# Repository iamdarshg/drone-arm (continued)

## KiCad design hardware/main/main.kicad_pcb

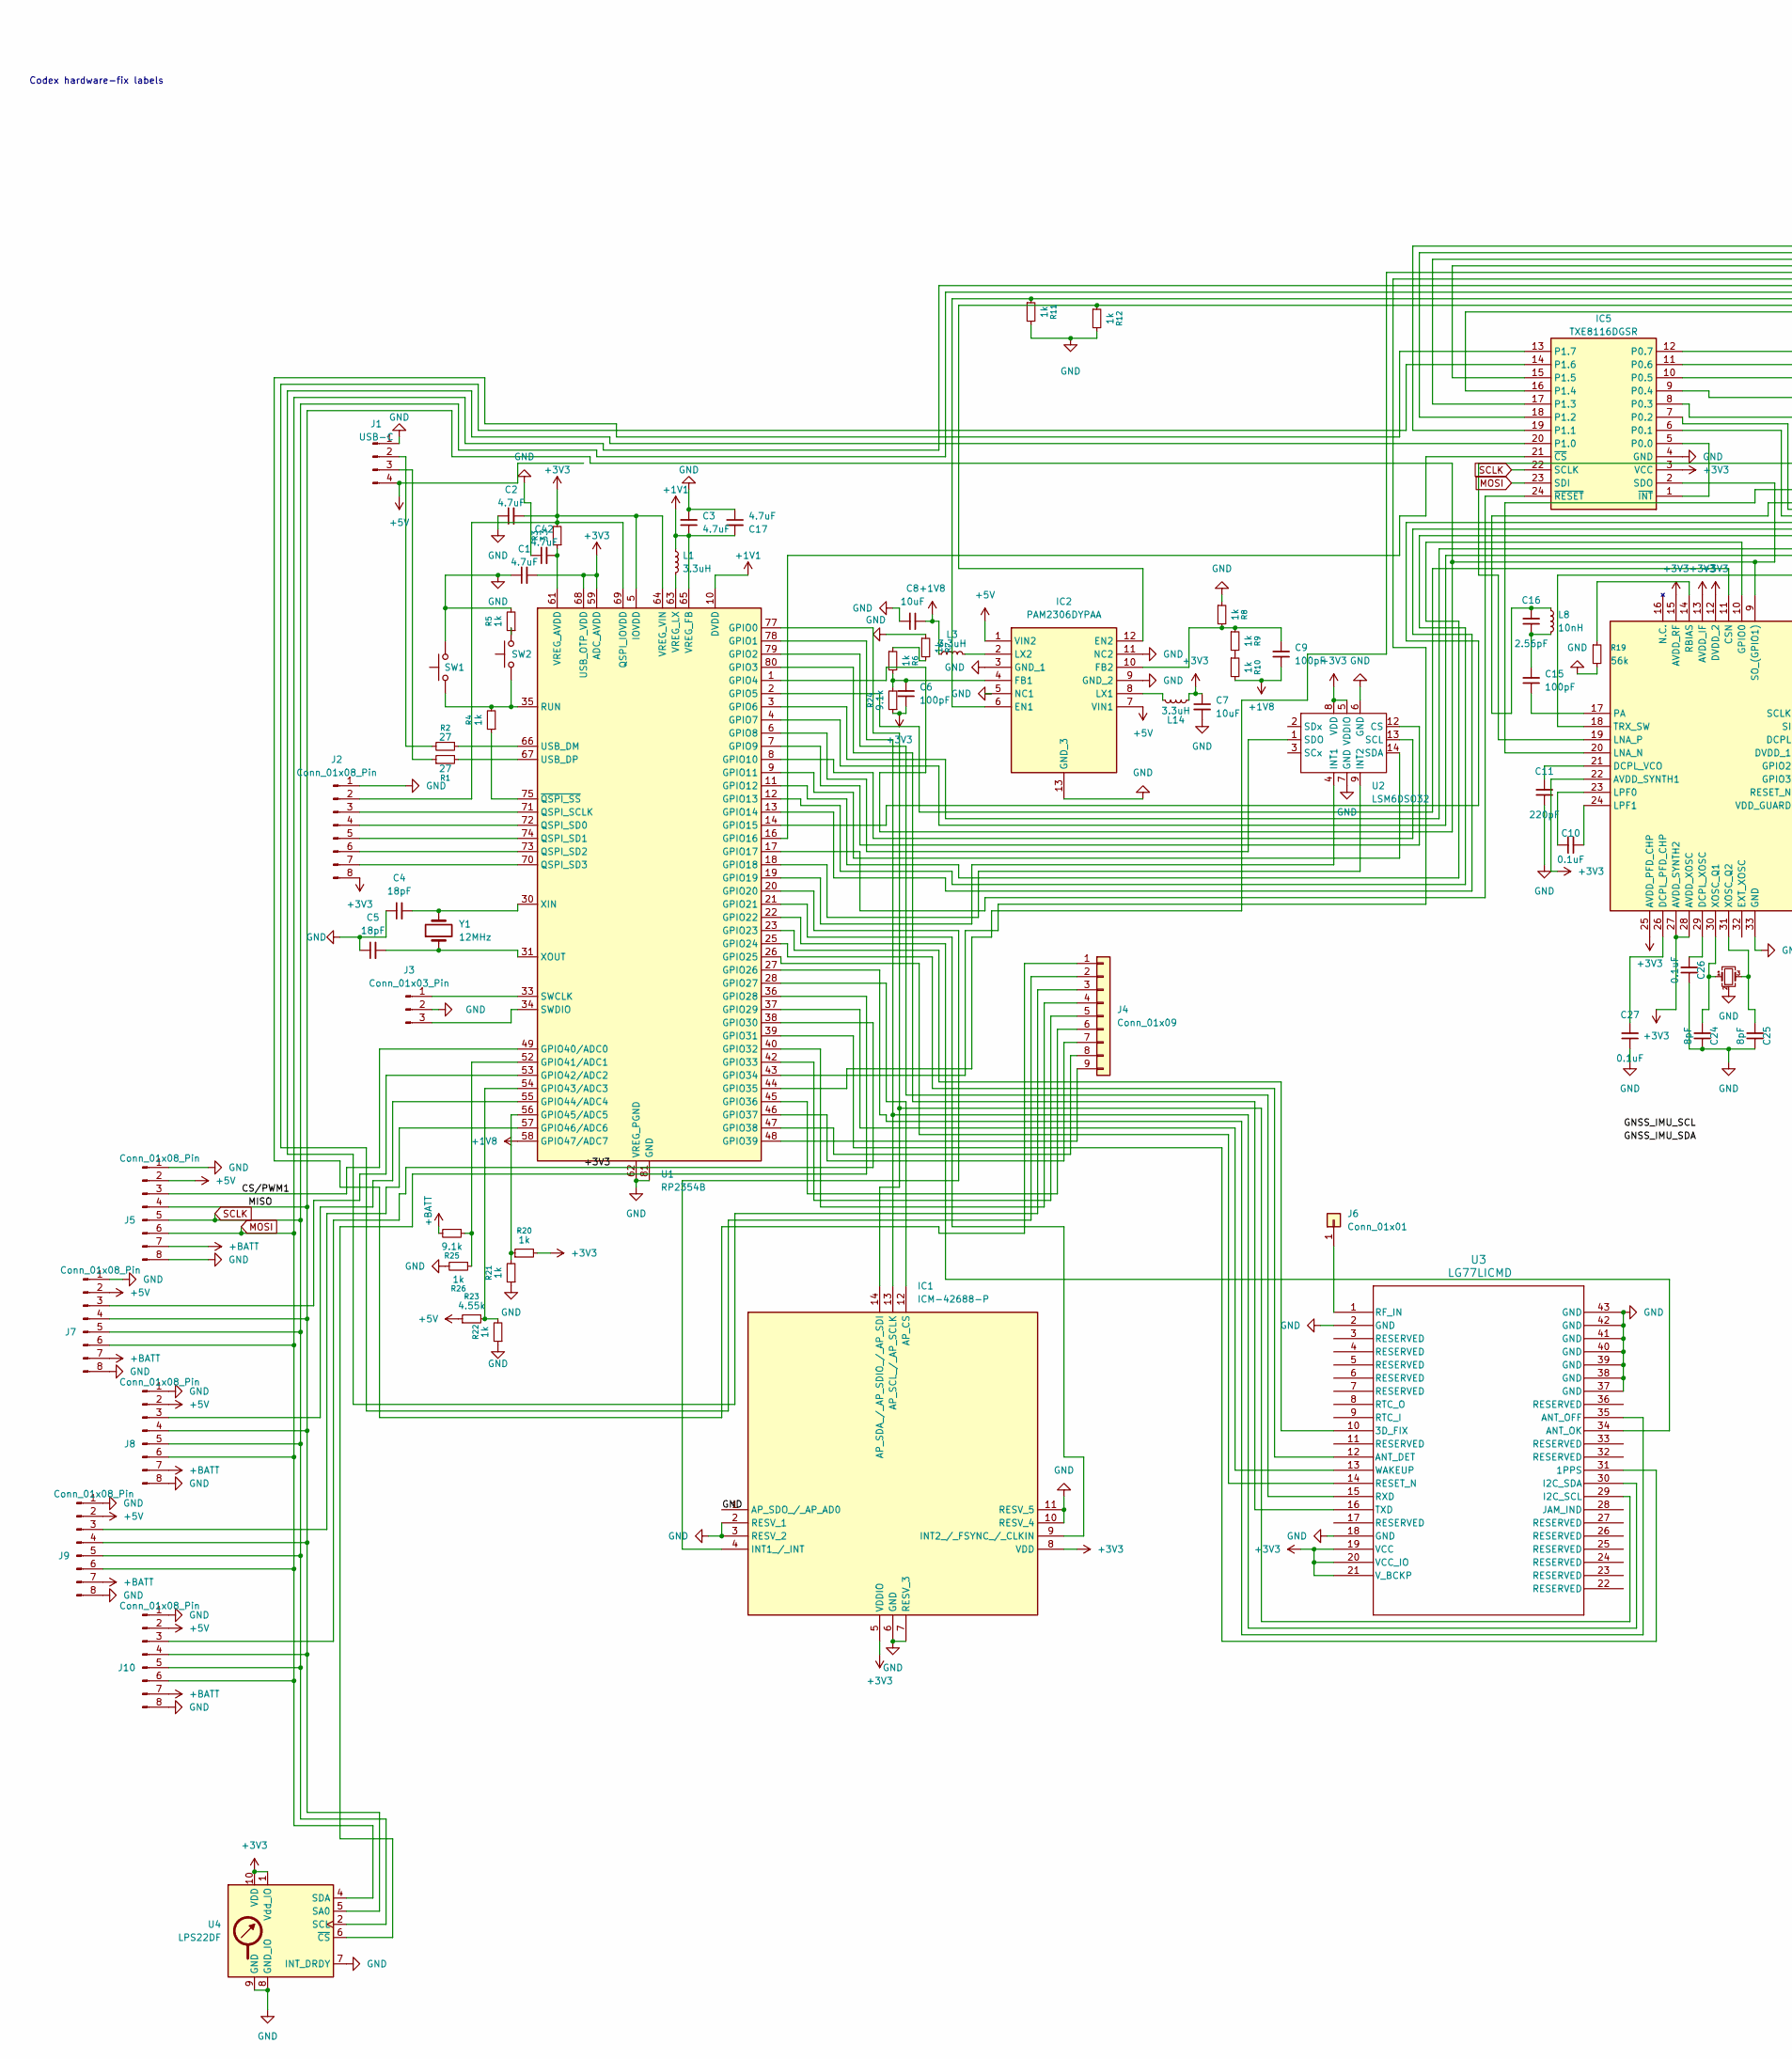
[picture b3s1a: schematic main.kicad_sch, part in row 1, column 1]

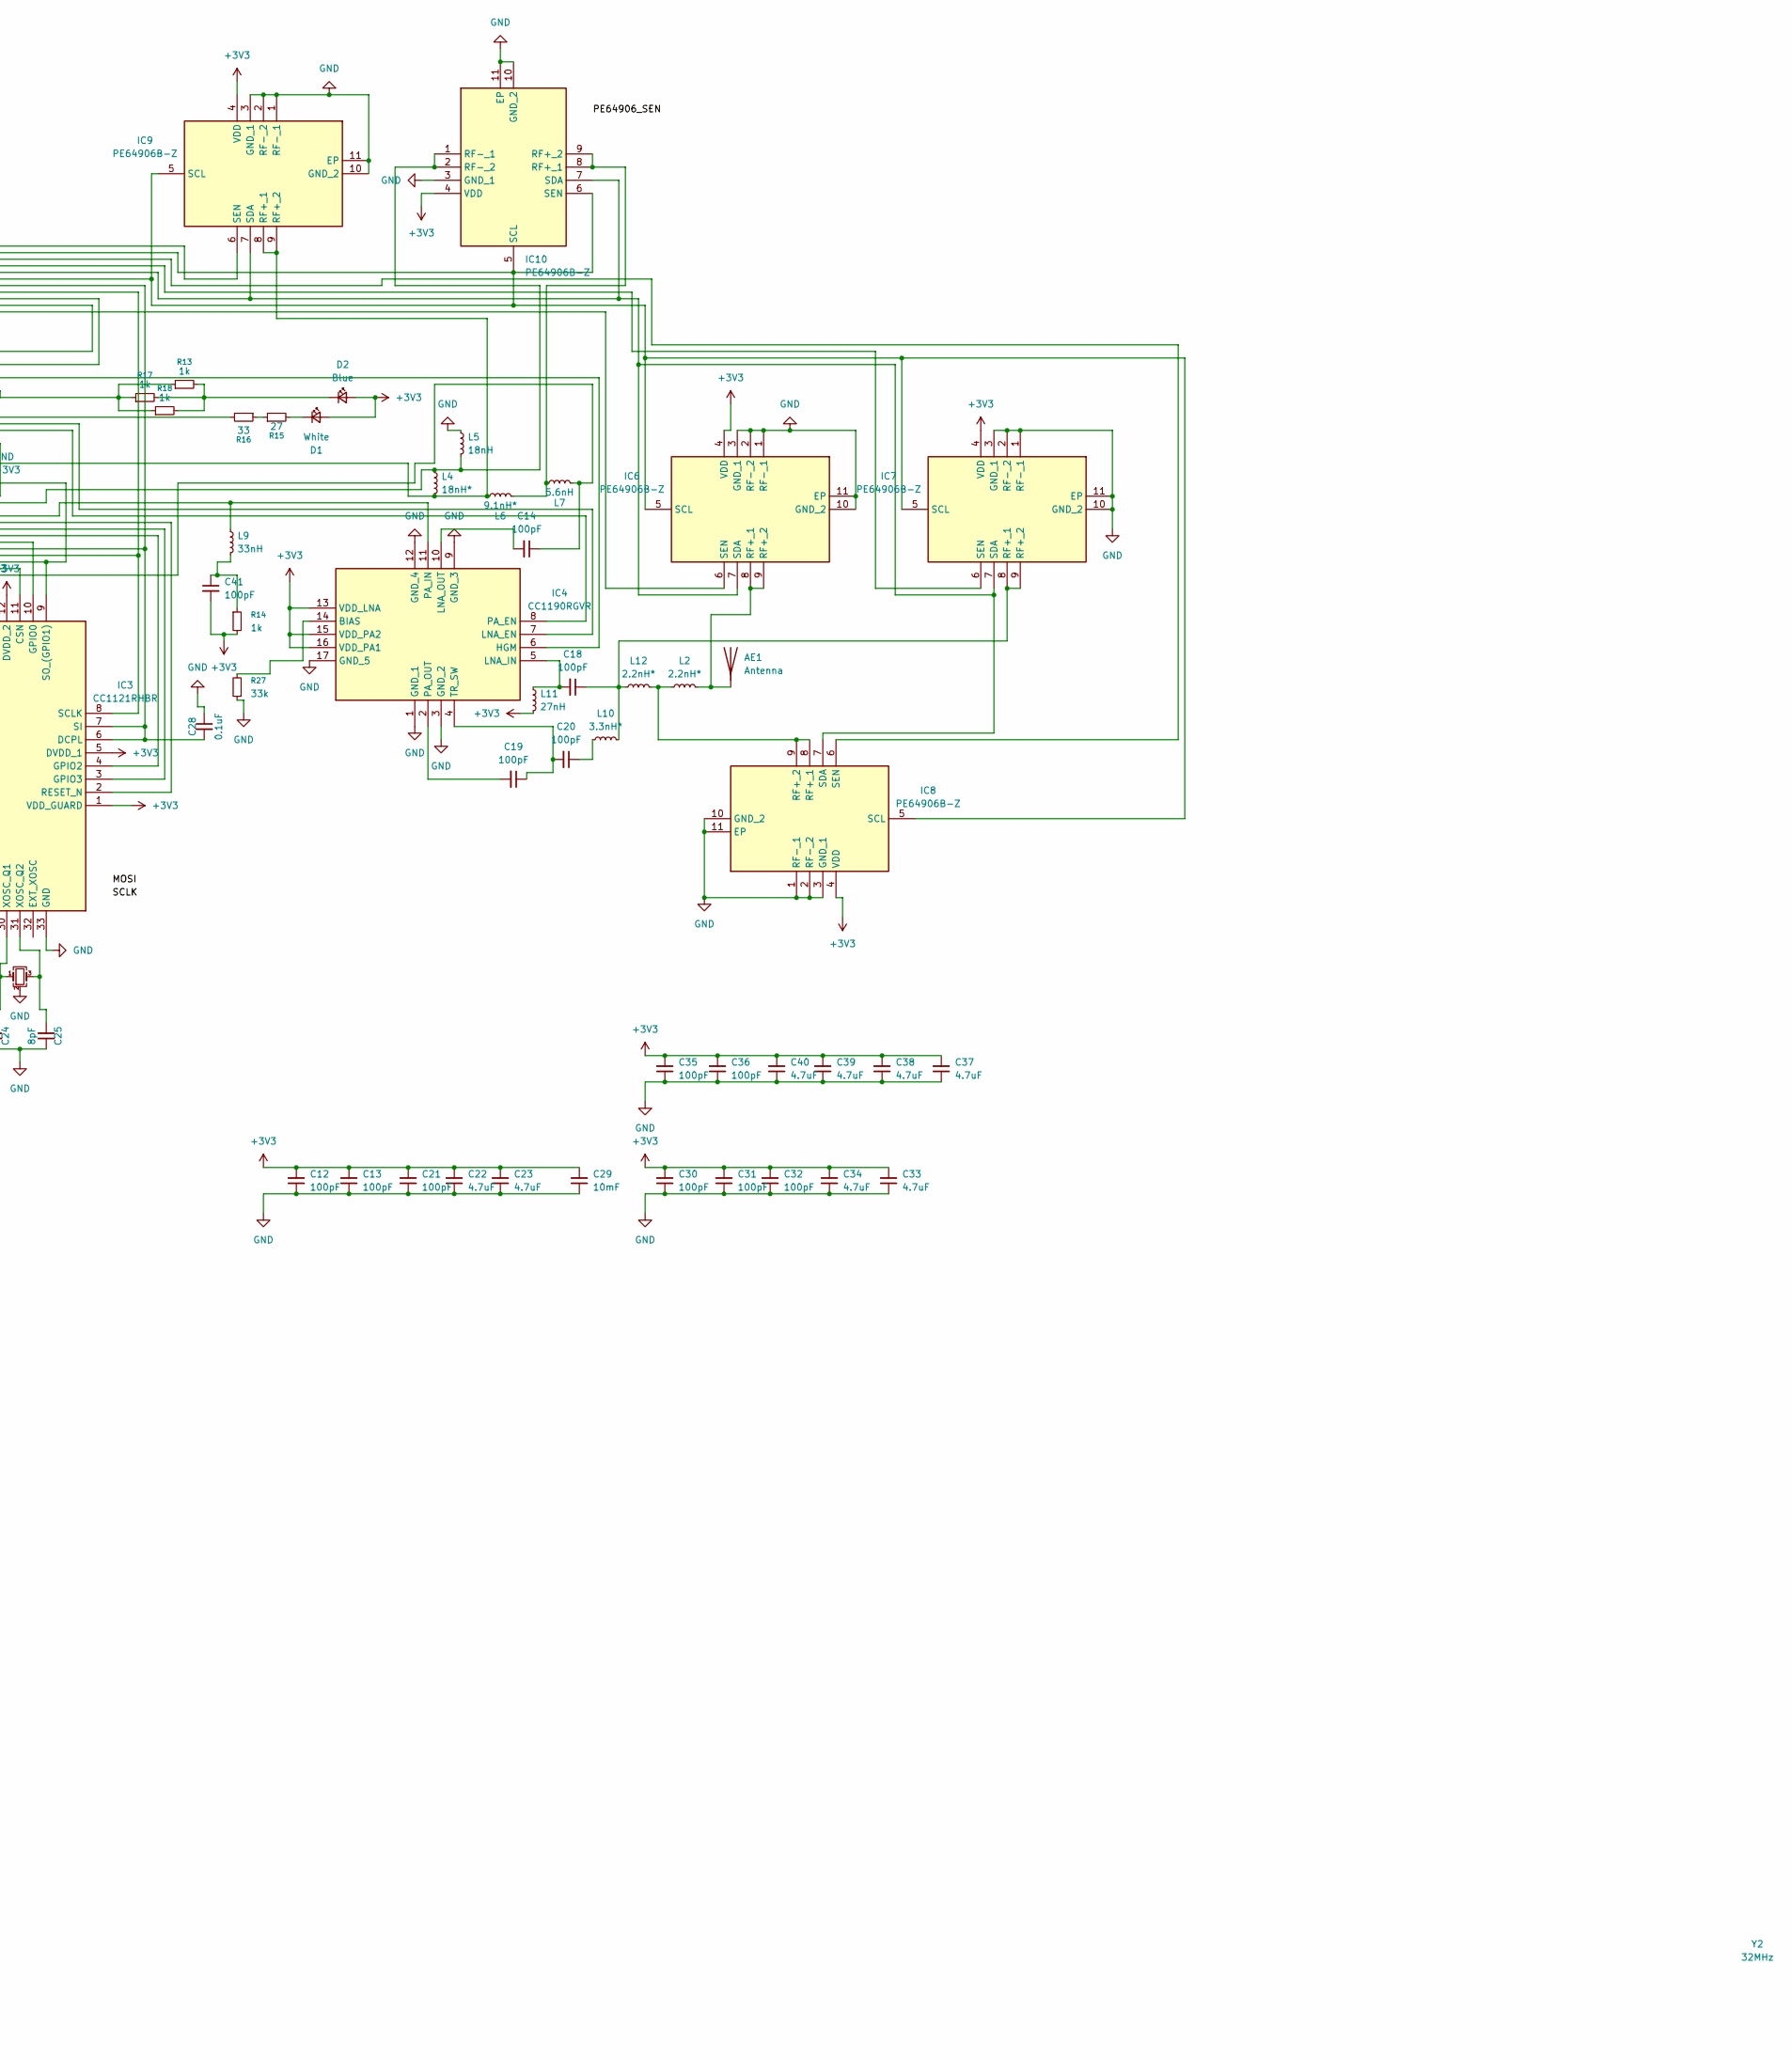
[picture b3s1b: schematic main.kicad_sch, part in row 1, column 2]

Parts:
AE1: Antenna; Texas_SWRA416_868MHz_915MHz
C1, C2, C3, C17, C22, C23, C33, C34, C37, C38, C39, C40, C42: 4.7uF; C_0805_2012Metric
C4, C5: 18pF; C_0402_1005Metric
C6, C9, C12, C13, C14, C15, C18, C19, C20, C21, C30, C31, C32, C35, C36, C41: 100pF; C_0201_0603Metric
C7, C8: 10uF; C_0805_2012Metric
C10, C26, C27, C28: 0.1uF; C_0201_0603Metric
C11: 220pF; C_0402_1005Metric
C16: 2.56pF; C_0201_0603Metric
C24, C25: 8pF; C_0402_1005Metric
C29: 10mF; CP_Radial_D5.0mm_P2.50mm
D1: White; LED_0201_0603Metric
D2: Blue; LED_0201_0603Metric
IC1: ICM-42688-P; IIM42352; Manufacturer_Part_Number ICM-42688-P; Mouser Part Number 410-ICM-42688-P
IC2: PAM2306DYPAA; SON45P300X300X80-13N; Manufacturer_Part_Number PAM2306DYPAA; Mouser Part Number 621-PAM2306DYPAA
IC3: CC1121RHBR; QFN50P500X500X100-33N-D; Manufacturer_Part_Number CC1121RHBR; Mouser Part Number 595-CC1121RHBR
IC4: CC1190RGVR; QFN65P400X400X100-17N-D; Manufacturer_Part_Number CC1190RGVR; Mouser Part Number 595-CC1190RGVR
IC5: TXE8116DGSR; SOP50P490X110-24N; Manufacturer_Part_Number TXE8116DGSR
IC6, IC7, IC8, IC9, IC10: PE64906B-Z; QFN50P200X200X60-11N-D; Manufacturer_Part_Number PE64906B-Z; Mouser Part Number 81-PE64906B-Z
J1: USB-C; PinHeader_1x04_P2.54mm_Vertical
J2: Conn_01x08_Pin; PinHeader_2x04_P1.27mm_Vertical
J3: Conn_01x03_Pin; PinHeader_1x03_P2.54mm_Vertical
J4: Conn_01x09; PinHeader_1x09_P2.54mm_Vertical
J5, J7, J8, J9, J10: Conn_01x08_Pin; PinHeader_1x08_P1.27mm_Vertical
J6: Conn_01x01; SolderWire-0.5sqmm_1x01_D0.9mm_OD2.3mm
L1: 3.3uH; L_0806_2016Metric
L2, L12: 2.2nH*; L_0402_1005Metric
L3, L14: 3.3uH; L_1210_3225Metric_Pad1.42x2.65mm_HandSolder
L4: 18nH*; L_01005_0402Metric
L5: 18nH; L_01005_0402Metric
L6: 9.1nH*; L_0402_1005Metric
L7: 5.6nH; L_0402_1005Metric
L8: 10nH; L_0805_2012Metric
L9: 33nH; L_0402_1005Metric
L10: 3.3nH*; L_0201_0603Metric
L11: 27nH; L_0201_0603Metric
R1, R2, R15: 27; R_0402_1005Metric
R3, R16: 33; R_1206_3216Metric
R4, R5, R6, R7, R8, R9, R10, R11, R12, R13, R14, R17, R18, R20, R21, R22, R26: 1k; R_0201_0603Metric
R19: 56k; R_0402_1005Metric
R23: 4.55k
R24, R25: 9.1k; R_0201_0603Metric
R27: 33k; R_0201_0603Metric
SW1, SW2: SW_Push; PinHeader_1x02_P2.54mm_Vertical
U1: RP2354B; QFN-80-1EP_10x10mm_P0.4mm_EP3.4x3.4mm
U2: LSM6DSO32; LGA-14_3x2.5mm_P0.5mm_LayoutBorder3x4y
U3: LG77LICMD; LG77L_QWS
U4: LPS22DF; ST_HLGA-10_2x2mm_P0.5mm_LayoutBorder3x2y
Y1: 12MHz; Crystal_SMD_ECS_CSM3X-2Pin_7.6x4.1mm
Y2: 32MHz; Crystal_SMD_3225-4Pin_3.2x2.5mm

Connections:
+1V1: C3.1, C17.2, L1.1, U1.10 (DVDD), U1.32 (DVDD), U1.51 (DVDD), U1.65 (VREG_FB)
+1V8: C8.1, C9.1, L3.1, R10.2, U1.58 (GPIO47/ADC7)
+3V3: C1.2, C2.2, C6.1, C7.1, C12.2, C13.2, C21.2, C22.2, C23.2, C29.2, C30.2, C31.2, C32.2, C33.2, C34.2, C35.2, C36.2, C37.2, C38.2, C39.2, C40.2, C41.2, D1.2 (A), D2.2 (A), IC1.5 (VDDIO), IC1.8 (VDD), IC3.1 (VDD_GUARD), IC3.5 (DVDD_1), IC3.12 (DVDD_2), IC3.13 (AVDD_IF), IC3.15 (AVDD_RF), IC3.22 (AVDD_SYNTH1), IC3.25 (AVDD_PFD_CHP), IC3.27 (AVDD_SYNTH2), IC3.28 (AVDD_XOSC), IC4.13 (VDD_LNA), IC4.15 (VDD_PA2), IC4.16 (VDD_PA1), IC5.3 (VCC), IC6.4 (VDD), IC7.4 (VDD), IC8.4 (VDD), IC9.4 (VDD), IC10.4 (VDD), J2.2, J2.8, L11.2, L14.1, R3.2, R14.2, R20.2, R24.1, U1.5 (IOVDD), U1.15 (IOVDD), U1.24 (IOVDD), U1.29 (IOVDD), U1.41 (IOVDD), U1.50 (IOVDD), U1.59 (ADC_AVDD), U1.60 (IOVDD), U1.64 (VREG_VIN), U1.68 (USB_OTP_VDD), U1.69 (QSPI_IOVDD), U1.76 (IOVDD), U2.5 (VDDIO), U2.8 (VDD), U3.19 (VCC), U3.20 (VCC_IO), U3.21 (V_BCKP), U4.1 (Vdd_IO), U4.10 (VDD)
+5V: IC2.1 (VIN2), IC2.7 (VIN1), J1.4, J5.2, J7.2, J8.2, J9.2, J10.2, R23.1
+BATT: J5.7, J7.7, J8.7, J9.7, J10.7, R25.2
/CS/PWM1: J5.3, U1.49 (GPIO40/ADC0)
/MISO: IC3.9 (SO_(GPIO1)), IC5.2 (SDO), J5.4, J7.4, J8.4, J9.4, J10.4, U1.1 (GPIO4), U4.5 (SA0)
/SCLK: IC3.8 (SCLK), IC5.22 (SCLK), J5.5, J7.5, J8.5, J9.5, J10.5, U1.4 (GPIO7), U4.2 (SCL)
GND: C1.1, C2.1, C3.2, C4.1, C5.1, C7.2, C8.2, C11.1, C12.1, C13.1, C17.1, C21.1, C22.1, C23.1, C24.1, C25.1, C26.1, C27.1, C28.1, C29.1, C30.1, C31.1, C32.1, C33.1, C34.1, C35.1, C36.1, C37.1, C38.1, C39.1, C40.1, C42.1, IC1.1 (AP_SDO_/_AP_AD0), IC1.2 (RESV_1), IC1.3 (RESV_2), IC1.6 (GND), IC1.7 (RESV_3), IC1.10 (RESV_4), IC1.11 (RESV_5), IC2.3 (GND_1), IC2.5 (NC1), IC2.9 (GND_2), IC2.11 (NC2), IC2.13 (GND_3), IC3.33 (GND), IC4.1 (GND_1), IC4.3 (GND_2), IC4.9 (GND_3), IC4.12 (GND_4), IC4.17 (GND_5), IC5.4 (GND), IC6.1 (RF-_1), IC6.2 (RF-_2), IC6.3 (GND_1), IC6.10 (GND_2), IC6.11 (EP), IC7.1 (RF-_1), IC7.2 (RF-_2), IC7.3 (GND_1), IC7.10 (GND_2), IC7.11 (EP), IC8.1 (RF-_1), IC8.2 (RF-_2), IC8.3 (GND_1), IC8.10 (GND_2), IC8.11 (EP), IC9.1 (RF-_1), IC9.2 (RF-_2), IC9.3 (GND_1), IC9.10 (GND_2), IC9.11 (EP), IC10.3 (GND_1), IC10.10 (GND_2), IC10.11 (EP), J1.1, J2.1, J3.2, J5.1, J5.8, J7.1, J7.8, J8.1, J8.8, J9.1, J9.8, J10.1, J10.8, L5.1, R5.2, R7.1, R8.1, R11.2, R12.2, R19.2, R21.1, R22.1, R26.2, R27.1, SW1.2, U1.62 (VREG_PGND), U1.81 (GND), U2.6 (GND), U2.7 (GND), U3.2 (GND), U3.18 (GND), U3.37 (GND), U3.38 (GND), U3.39 (GND), U3.40 (GND), U3.41 (GND), U3.42 (GND), U3.43 (GND), U4.3 (GND), U4.7 (INT_DRDY), U4.8 (GND_IO), U4.9 (GND), Y2.2 (G), Y2.4 (G)
unnamed: AE1.1 (A), IC6.8 (RF+_1), IC6.9 (RF+_2), L2.2
unnamed: C15.2, C16.1, L8.2
unnamed: C20.1, L10.1
unnamed: C41.1, L9.2, R14.1
unnamed: D1.1 (K), R15.2
unnamed: D2.1 (K), R13.2, R17.2, R18.2
unnamed: IC1.12 (AP_CS), U1.28 (GPIO27)
unnamed: IC1.4 (INT1_/_INT), U1.20 (GPIO20)
unnamed: IC1.9 (INT2_/_FSYNC_/_CLKIN), U1.21 (GPIO21)
unnamed: IC2.6 (EN1), IC5.11 (P0.6), R11.1
unnamed: IC2.12 (EN2), IC5.12 (P0.7), R12.1
unnamed: C6.2, IC2.4 (FB1), R6.2, R24.2
unnamed: C9.2, IC2.10 (FB2), R8.2, R9.1
unnamed: IC2.8 (LX1), L14.2
unnamed: IC2.2 (LX2), L3.2
unnamed: IC3.11 (CSN), U1.2 (GPIO5)
unnamed: C27.2, IC3.26 (DCPL_PFD_CHP)
unnamed: C11.2, IC3.21 (DCPL_VCO)
unnamed: C26.2, IC3.29 (DCPL_XOSC)
unnamed: IC3.10 (GPIO0), U1.11 (GPIO12)
unnamed: IC3.4 (GPIO2), U1.12 (GPIO13)
unnamed: IC3.3 (GPIO3), U1.13 (GPIO14)
unnamed: IC3.19 (LNA_P), IC9.8 (RF+_1), IC9.9 (RF+_2), L4.2, L6.1
unnamed: C10.2, IC3.23 (LPF0)
unnamed: C10.1, IC3.24 (LPF1)
unnamed: C15.1, IC3.17 (PA)
unnamed: IC3.14 (RBIAS), R19.1
unnamed: IC3.2 (RESET_N), U1.14 (GPIO15)
unnamed: C14.1, IC3.18 (TRX_SW), L7.2
unnamed: C24.2, IC3.30 (XOSC_Q1), Y2.1
unnamed: C25.2, IC3.31 (XOSC_Q2), Y2.3
unnamed: IC4.14 (BIAS), R27.2
unnamed: IC4.6 (HGM), IC5.10 (P0.5)
unnamed: IC4.7 (LNA_EN), IC5.7 (P0.2)
unnamed: C18.2, IC4.5 (LNA_IN), L11.1
unnamed: C14.2, IC4.10 (LNA_OUT)
unnamed: IC4.8 (PA_EN), IC5.6 (P0.1)
unnamed: C16.2, IC4.11 (PA_IN), L8.1, L9.1
unnamed: C19.2, IC4.2 (PA_OUT)
unnamed: C19.1, C20.2, IC4.4 (TR_SW)
unnamed: IC5.1 (~INT), IC5.5 (P0.0)
unnamed: IC5.8 (P0.3), R16.2
unnamed: IC5.9 (P0.4), R13.1, R17.1, R18.1
unnamed: IC5.20 (P1.0), J4.3
unnamed: IC5.19 (P1.1), IC9.6 (SEN)
unnamed: IC5.17 (P1.3), IC8.6 (SEN)
unnamed: IC5.16 (P1.4), IC6.6 (SEN)
unnamed: IC5.15 (P1.5), IC7.6 (SEN)
unnamed: IC5.14 (P1.6), J4.2
unnamed: IC5.13 (P1.7), J4.1
unnamed: IC5.21 (~CS), U1.16 (GPIO16)
unnamed: IC5.24 (~RESET), U1.17 (GPIO17)
unnamed: C18.1, IC7.8 (RF+_1), IC7.9 (RF+_2), L10.2, L12.1
unnamed: IC8.8 (RF+_1), IC8.9 (RF+_2), L2.1, L12.2
unnamed: IC10.8 (RF+_1), IC10.9 (RF+_2), L6.2, L7.1
unnamed: IC3.20 (LNA_N), IC10.1 (RF-_1), IC10.2 (RF-_2), L4.1, L5.2
unnamed: IC6.7 (SDA), IC7.7 (SDA), IC8.7 (SDA), IC9.7 (SDA), IC10.7 (SDA), U1.44 (GPIO35)
unnamed: J1.2, R2.2
unnamed: J1.3, R1.1
unnamed: J2.3, U1.71 (QSPI_SCLK)
unnamed: J2.4, U1.72 (QSPI_SD0)
unnamed: J2.5, U1.74 (QSPI_SD1)
unnamed: J2.6, U1.73 (QSPI_SD2)
unnamed: J2.7, U1.70 (QSPI_SD3)
unnamed: J3.1, U1.33 (SWCLK)
unnamed: J3.3, U1.34 (SWDIO)
unnamed: J4.4, U1.40 (GPIO32)
unnamed: J4.5, U1.42 (GPIO33)
unnamed: J4.6, U1.45 (GPIO36)
unnamed: J4.7, U1.46 (GPIO37)
unnamed: J4.8, U1.47 (GPIO38)
unnamed: J4.9, U1.48 (GPIO39)
unnamed: J6.1, U3.1 (RF_IN)
unnamed: J7.3, U1.53 (GPIO42/ADC2)
unnamed: J8.3, U1.55 (GPIO44/ADC4)
unnamed: J9.3, U1.57 (GPIO46/ADC6)
unnamed: J10.3, U1.38 (GPIO30)
unnamed: R5.1, SW2.2
unnamed: R6.1, R7.2
unnamed: R9.2, R10.1
unnamed: R15.1, R16.1
unnamed: U1.79 (GPIO2), U3.15 (RXD)
unnamed: U1.80 (GPIO3), U3.16 (TXD)
unnamed: U1.6 (GPIO8), U2.1 (SDO)
unnamed: U1.7 (GPIO9), U2.12 (CS)
unnamed: U1.8 (GPIO10), U2.13 (SCL)
unnamed: U1.9 (GPIO11), U2.14 (SDA)
unnamed: U1.18 (GPIO18), U2.9 (INT2)
unnamed: U1.19 (GPIO19), U2.4 (INT1)
unnamed: U1.22 (GPIO22), U3.34 (ANT_OK)
unnamed: U1.23 (GPIO23), U3.10 (3D_FIX)
unnamed: U1.25 (GPIO24), U3.12 (ANT_DET)
unnamed: U1.26 (GPIO25), U3.14 (RESET_N)
unnamed: U1.27 (GPIO26), U3.35 (ANT_OFF)
unnamed: U1.36 (GPIO28), U4.6 (~CS)
unnamed: U1.37 (GPIO29), U3.13 (WAKEUP)
unnamed: U1.39 (GPIO31), U3.31 (1PPS)
unnamed: R25.1, R26.1, U1.52 (GPIO41/ADC1)
unnamed: R22.2, R23.2, U1.54 (GPIO43/ADC3)
unnamed: R20.1, R21.2, U1.56 (GPIO45/ADC5)
unnamed: R4.2, SW1.1, SW2.1, U1.35 (RUN)
unnamed: R2.1, U1.66 (USB_DM)
unnamed: R1.2, U1.67 (USB_DP)
unnamed: C42.2, R3.1, U1.61 (VREG_AVDD)
unnamed: L1.2, U1.63 (VREG_LX)
unnamed: C4.2, U1.30 (XIN), Y1.2
unnamed: C5.2, U1.31 (XOUT), Y1.1
unnamed: R4.1, U1.75 (~QSPI_SS)

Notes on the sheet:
Codex hardware-fix labels

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
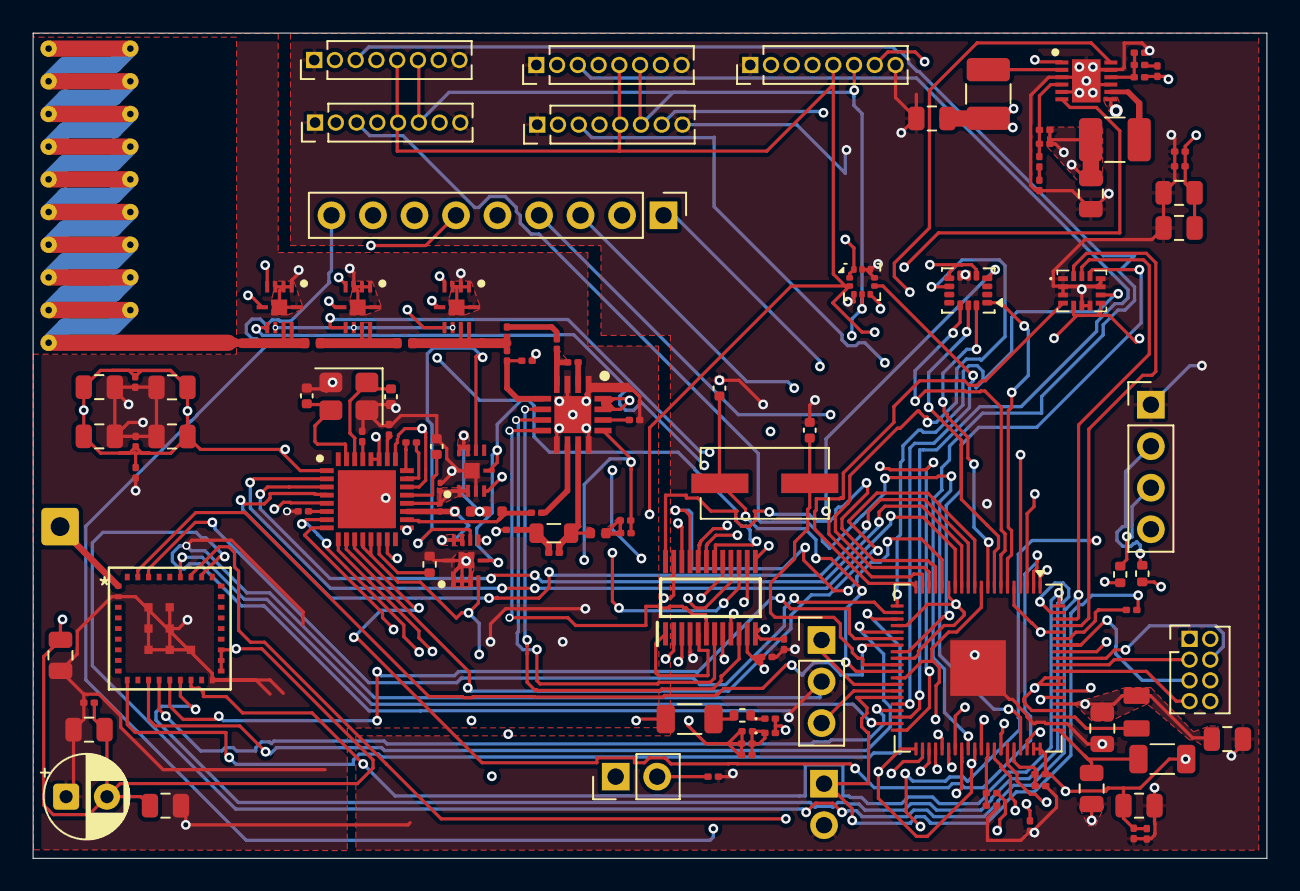
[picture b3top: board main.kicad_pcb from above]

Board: 4 copper layers, 75.5 x 50.5 mm, 112 parts (1 on the bottom side), 122 nets.

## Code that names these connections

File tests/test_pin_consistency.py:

#!/usr/bin/env python3
"""Pin-consistency test: firmware pin map vs PCB netlist pin map.

Firmware source of truth: src/board_config.h on the sdk-recreation branch.
This test reads hardware/main/rev_b/mcu_pinmap.json (generated from the
schematic netlist) and asserts that every firmware pin assignment matches
the PCB.  Run with: pytest tests/test_pin_consistency.py
"""
import json
import subprocess
import sys
from pathlib import Path

REPO = Path(__file__).resolve().parents[1]
PINMAP = REPO / "hardware/main/rev_b/mcu_pinmap.json"

# Firmware pin assignments (RP2354B GPIO numbers).
# Source: sdk-recreation branch, src/board_config.h + main Rev-B interface spec.
# The firmware repo keeps these in board_config.h; they are mirrored here so the
# test fails loudly if either side drifts.
FIRMWARE_PINS = {
    "SENS_SCLK": 0,
    "SENS_MOSI": 1,
    "SENS_MISO": 2,
    "ICM_nCS": 3,
    "LSM_nCS": 4,
    "ICM_INT1": 5,
    "ICM_INT2": 6,
    "LSM_INT1": 7,
    "LSM_INT2": 8,
    "BARO_SCL": 9,
    "BARO_SDA": 10,
    "BARO_DRDY": 11,
    "GNSS_TX": 12,
    "GNSS_RX": 13,
    "GNSS_PPS": 14,
    "GNSS_RESET_N": 15,
    "RF_SCLK": 16,
    "RF_MOSI": 17,
    "RF_MISO": 18,
    "RF_nCS": 19,
    "RF_RESET_N": 20,
    "RF_GPIO0": 21,
    "RF_GPIO2": 22,
    "RF_GPIO3": 23,
    "PA_EN": 24,
    "LNA_EN": 25,
    "HGM": 26,
    "CAN_SCK": 27,
    "CAN_MOSI": 28,
    "CAN_MISO": 29,
    "CAN_nCS": 30,
    "CAN_INT": 31,
    "STATUS_LED": 32,
    "GNSS_PWR_EN": 33,
    "PWM_ESC1": 34,
    "PWM_ESC2": 35,
    "PWM_ESC3": 36,
    "PWM_ESC4": 37,
    "PWM_ESC5": 38,
    "PWM_ESC6": 39,
}


def load_pcb_map():
    data = json.loads(PINMAP.read_text())
    out = {}
    for gpio, info in data["pins"].items():
        # normalise hierarchical net names to their leaf token
        leaf = info["net"].split("/")[-1]
        out.setdefault(leaf, []).append(int(gpio))
    return out


def test_pinmap_file_exists():
    assert PINMAP.exists(), "run tools/hardware/gen_main_pinmap.py first"


def test_every_firmware_pin_exists_on_pcb():
    pcb = load_pcb_map()
    missing = [n for n in FIRMWARE_PINS if n not in pcb]
    assert not missing, f"firmware pins absent from PCB: {missing}"


def test_gpio_numbers_match():
    pcb = load_pcb_map()
    wrong = {
        n: (FIRMWARE_PINS[n], pcb.get(n))
        for n in FIRMWARE_PINS
        if n in pcb and FIRMWARE_PINS[n] not in pcb[n]
    }
    assert not wrong, f"GPIO number mismatches firmware vs PCB: {wrong}"


def test_no_duplicate_gpio_assignment():
    seen = {}
    for n, g in FIRMWARE_PINS.items():
        assert g not in seen, f"GPIO{g} double-assigned: {seen[g]} and {n}"
        seen[g] = n


def test_esc_pwm_pins_are_contiguous():
    esc = [FIRMWARE_PINS[f"PWM_ESC{i}"] for i in range(1, 7)]
    assert esc == sorted(esc), "ESC PWM pins must be ascending"

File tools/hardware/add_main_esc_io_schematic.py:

#!/usr/bin/env python3
"""Surgically add six standard PWM ESC connectors to Main Rev B schematics."""

from __future__ import annotations

import re
import uuid
from pathlib import Path


ROOT = Path(__file__).resolve().parents[2]
MAIN_DIR = ROOT / "hardware" / "main" / "rev_b"
MCU_PATH = MAIN_DIR / "mcu.kicad_sch"
TOP_PATH = MAIN_DIR / "main_rev_b.kicad_sch"


def new_uuid() -> str:
    return str(uuid.uuid4())


def number(value: float) -> str:
    rounded = round(value, 4)
    if rounded == int(rounded):
        return str(int(rounded))
    return f"{rounded:.4f}".rstrip("0").rstrip(".")


def sexpr_end(text: str, start: int) -> int:
    depth = 0
    in_string = False
    escaped = False
    for index in range(start, len(text)):
        char = text[index]
        if in_string:
            if escaped:
                escaped = False
            elif char == "\\":
                escaped = True
            elif char == '"':
                in_string = False
            continue
        if char == '"':
            in_string = True
        elif char == "(":
            depth += 1
        elif char == ")":
            depth -= 1
            if depth == 0:
                return index + 1
    raise ValueError("Unbalanced KiCad S-expression")


def find_block(text: str, start_pattern: str, contains: str) -> tuple[int, int, str]:
    for match in re.finditer(start_pattern, text, flags=re.MULTILINE):
        start = match.start()
        end = sexpr_end(text, start)
        block = text[start:end]
        if contains in block:
            return start, end, block
    raise ValueError(f"Could not find block containing {contains!r}")


def wire_block(x1: float, y1: float, x2: float, y2: float) -> str:
    return (
        "\t(wire\n"
        "\t\t(pts\n"
        f"\t\t\t(xy {number(x1)} {number(y1)}) (xy {number(x2)} {number(y2)})\n"
        "\t\t)\n"
        "\t\t(stroke\n"
        "\t\t\t(width 0)\n"
        "\t\t\t(type default)\n"
        "\t\t)\n"
        f"\t\t(uuid \"{new_uuid()}\")\n"
        "\t)\n"
    )


def label_block(name: str, x: float, y: float, rotation: int = 0, size: float = 0.9) -> str:
    return (
        f"\t(label \"{name}\"\n"
        f"\t\t(at {number(x)} {number(y)} {rotation})\n"
        "\t\t(effects\n"
        "\t\t\t(font\n"
        f"\t\t\t\t(size {number(size)} {number(size)})\n"
        "\t\t\t)\n"
        "\t\t\t(justify left bottom)\n"
        "\t\t)\n"
        f"\t\t(uuid \"{new_uuid()}\")\n"
        "\t)\n"
    )


def hierarchical_label_block(name: str, y: float) -> str:
    return (
        f"\n\t(hierarchical_label \"{name}\"\n"
        "\t\t(shape input)\n"
        f"\t\t(at 20.32 {number(y)} 0.0000)\n"
        "\t\t(effects\n"
        "\t\t\t(font\n"
        "\t\t\t\t(size 0.9 0.9)\n"
        "\t\t\t)\n"
        "\t\t\t(justify left)\n"
        "\t\t)\n"
        f"\t\t(uuid \"{new_uuid()}\")\n"
        "\t)"
    )


def sheet_pin_block(name: str, x: float, y: float, rotation: int, justify: str) -> str:
    return (
        f"\t\t(pin \"{name}\" bidirectional\n"
        f"\t\t\t(at {number(x)} {number(y)} {rotation})\n"
        f"\t\t\t(uuid \"{new_uuid()}\")\n"
        "\t\t\t(effects\n"
        "\t\t\t\t(font\n"
        "\t\t\t\t\t(size 1.27 1.27)\n"
        "\t\t\t\t)\n"
        f"\t\t\t\t(justify {justify})\n"
        "\t\t\t)\n"
        "\t\t)\n"
    )


AT_PATTERN = re.compile(r"\(at (-?\d+(?:\.\d+)?) (-?\d+(?:\.\d+)?) ([^)]+)\)")
UUID_PATTERN = re.compile(r'\(uuid "[0-9a-f-]+"\)')


def clone_connector(template: str, reference: str, value: str, x: float, y: float) -> str:
    dx = x - 44.45
    dy = y - 149.86

    def shift(match: re.Match[str]) -> str:
        return (
            f"(at {number(float(match.group(1)) + dx)} "
            f"{number(float(match.group(2)) + dy)} {match.group(3)})"
        )

    block = AT_PATTERN.sub(shift, template)
    block = block.replace('"J10"', f'"{reference}"')
    block = block.replace('"SWD"', f'"{value}"')
    block = block.replace(
        '"Connector_JST:JST_SH_SM03B-SRSS-TB_1x03-1MP_P1.00mm_Horizontal"',
        '"Connector_PinHeader_2.54mm:PinHeader_1x03_P2.54mm_Vertical"',
    )
    return UUID_PATTERN.sub(lambda _: f'(uuid "{new_uuid()}")', block)


def add_mcu_connectors() -> None:
    text = MCU_PATH.read_text(encoding="utf-8")
    if 'property "Reference" "J60"' in text:
        raise RuntimeError("PWM ESC connectors are already present in mcu.kicad_sch")

    symbol_start = r'^\t\(symbol\s*$'
    _, j10_end, j10 = find_block(text, symbol_start, 'property "Reference" "J10"')
    symbols = []
    connector_labels = []
    for index in range(1, 7):
        x = 35.56 + (index - 1) * 35.56
        y = 195.58
        symbols.append(clone_connector(j10, f"J{59 + index}", f"ESC_PWM_{index}", x, y))
        pin_x = x - 5.08
        connector_labels.extend(
            (
                label_block("CAN_GND", pin_x, y - 2.54, 180),
                label_block("CAN_5V", pin_x, y, 180),
                label_block(f"PWM_ESC{index}", pin_x, y + 2.54, 180),
            )
        )
    text = text[:j10_end] + "\n" + "\n".join(symbols) + text[j10_end:]

    for y in (93.98, 96.52, 99.06, 101.6, 104.14, 106.68):
        pattern = re.compile(
            rf"\n\t\(no_connect\n\t\t\(at 87\.63 {re.escape(number(y))}\)\n"
            rf"\t\t\(uuid \"[0-9a-f-]+\"\)\n\t\)",
        )
        text, count = pattern.subn("", text, count=1)
        if count != 1:
            raise RuntimeError(f"Expected one no-connect marker at GPIO position {y}")

    first_label = text.index("\n\t(label ") + 1
    extra_wires = wire_block(20.32, 124.46, 25.40, 124.46)
    extra_wires += wire_block(20.32, 127.00, 25.40, 127.00)
    text = text[:first_label] + extra_wires + text[first_label:]

    first_hlabel = text.index("\n\t(hierarchical_label ") + 1
    pwm_labels = "".join(
        label_block(f"PWM_ESC{index}", 87.63, y, 180)
        for index, y in enumerate((93.98, 96.52, 99.06, 101.6, 104.14, 106.68), start=1)
    )
    local_labels = (
        label_block("CAN_5V", 25.40, 124.46, 0, 0.8)
        + label_block("CAN_GND", 25.40, 127.00, 0, 0.8)
        + pwm_labels
        + "".join(connector_labels)
    )
    text = text[:first_hlabel] + local_labels + text[first_hlabel:]

    can_int_start = text.index('\n\t(hierarchical_label "CAN_INT"') + 1
    can_int_end = sexpr_end(text, can_int_start)
    hlabels = hierarchical_label_block("CAN_5V", 124.46)
    hlabels += hierarchical_label_block("CAN_GND", 127.00)
    text = text[:can_int_end] + hlabels + text[can_int_end:]

    MCU_PATH.write_text(text, encoding="utf-8")


def add_top_sheet_pins() -> None:
    text = TOP_PATH.read_text(encoding="utf-8")
    old_text = (
        "Physically and electrically distinct from the ESC; CAN + protected 5 V are the only normal interconnects."
    )
    new_text = "CAN + protected 5 V serve the custom ESC; six PWM outputs support standard ESCs."
    if old_text not in text:
        raise RuntimeError("Expected Main Rev B title text was not found")
    text = text.replace(old_text, new_text, 1)

    sheet_start_pattern = r'^\t\(sheet\s*$'
    sheet_start, sheet_end, sheet = find_block(
        text, sheet_start_pattern, 'property "Sheetname" "RP2354B MCU"'
    )
    if 'pin "CAN_5V"' in sheet or 'pin "CAN_GND"' in sheet:
        raise RuntimeError("CAN power pins are already present on the MCU sheet")
    insert_at = sheet.index("\t\t(instances")
    pins = sheet_pin_block("CAN_5V", 287.02, 76.20, 0, "right")
    pins += sheet_pin_block("CAN_GND", 106.68, 78.74, 180, "left")
    sheet = sheet[:insert_at] + pins + sheet[insert_at:]
    text = text[:sheet_start] + sheet + text[sheet_end:]

    first_label = text.index("\n\t(label ") + 1
    wires = wire_block(287.02, 76.20, 289.56, 76.20)
    wires += wire_block(106.68, 78.74, 104.14, 78.74)
    text = text[:first_label] + wires + text[first_label:]

    title_index = text.index('\n\t(text "REV-B FLIGHT-CONTROL BOARD') + 1
    labels = label_block("CAN_5V", 289.56, 76.20, 0, 0.8)
    labels += label_block("CAN_GND", 104.14, 78.74, 0, 0.8)
    text = text[:title_index] + labels + text[title_index:]

    TOP_PATH.write_text(text, encoding="utf-8")


def main() -> None:
    add_mcu_connectors()
    add_top_sheet_pins()


if __name__ == "__main__":
    main()

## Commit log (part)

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2026-05-13 Auto-sync ESC PCB 2026-05-13 23:15:14
2026-05-13 Auto-sync ESC PCB 2026-05-13 23:17:03
2026-05-13 more pcb stuff
2026-05-13 Auto-sync ESC PCB 2026-05-13 23:25:39
2026-05-14 Auto-sync ESC PCB 2026-05-14 14:57:42
2026-05-14 Auto-sync ESC PCB 2026-05-14 18:54:00
2026-05-14 Auto-sync ESC PCB 2026-05-14 19:03:09
2026-05-14 Auto-sync ESC PCB 2026-05-14 19:41:35
2026-05-14 Auto-sync ESC PCB 2026-05-14 19:43:25
2026-05-14 Auto-sync ESC PCB 2026-05-14 19:44:52
2026-05-14 Auto-sync ESC PCB 2026-05-14 19:45:16
2026-05-14 Auto-sync ESC PCB 2026-05-14 19:52:13
2026-05-14 Auto-sync ESC PCB 2026-05-14 22:45:44
2026-05-14 Auto-sync ESC PCB 2026-05-14 23:15:03
2026-05-15 Auto-sync ESC PCB 2026-05-15 20:05:45
2026-05-16 Auto-sync ESC PCB 2026-05-16 17:15:06
2026-05-16 Auto-sync ESC PCB 2026-05-16 17:15:54
